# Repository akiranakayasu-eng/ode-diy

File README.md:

# ODE-DIY — 自作の Art-Net / sACN → DMX512 ノード

Art-Net と sACN（E1.31）を LAN で受けて DMX512 を出す、手作りの照明用ノード（「箱」）。照明操作ソフト miseru の画面を本体に内蔵し、ブラウザから WebSocket で照明を動かせる。

A DIY Art-Net / sACN to DMX512 node with a built-in web UI (miseru) over HTTP/WebSocket.

## 版

| 版 | マイコン | 状態 | 場所 |
|---|---|---|---|
| rev A | STM32F407VGT6 + LAN8742A（有線 LAN） | 基板を作って手実装 1 台が動いている。実機に書き込んで動いているのはファーム v0.3.0。このリポジトリのファームは v0.3.6（v0.3.1 以降は試験版（Linux）でだけ確認） | [hardware/revA](hardware/revA/) |
| rev B | ESP32-S3-WROOM-1-N16R8 + W5500（Wi-Fi と有線の併用） | **作業中**。本体の回路図と PCB、天板の回路図と PCB まで（どれも未発注で、まだ直している。版はそれぞれの README）。ファームはこれから | [hardware/revB](hardware/revB/) |

## フォルダ

- `hardware/revA/ode_main/` … rev A の KiCad 一式、ガーバー（JLCPCB 用 4 層）、部品リスト、レビューと立ち上げの記録
- `hardware/revA/case/` … ケース板（天板・底板、基板材で作る）
- `hardware/revB/ode_main/`・`ode_top/` … rev B の本体と天板の回路図・PCB、ケースの寸法モデル、構成案、点検記録
- `firmware/` … ファーム。機種に依らない部分（`app/`）と機種ごとの部分（`port/stm32/`、Linux で試す `port/host/`）に分かれている。rev B は `port/esp32/` を足す予定。ビルド・書き込み・試し方は [firmware/README.md](firmware/README.md)
- `docs/websocket-spec.md` … miseru と箱のあいだの WebSocket とロックの仕様
- `tools/` … 試験用の小さな道具（sACN の送信など）

## できること（rev A、ファーム v0.3.6）

- Art-Net 4（ArtPoll / ArtDmx）と sACN を受けて DMX 1 ユニバースを出す
- 本体に miseru の画面を内蔵（差し替え可）。WebSocket で操作し、送り手を 1 つにロックする
- `/setup` で PIN の変更と画面の差し替え（LOCK ボタン SW2 を 3 秒押してから 10 分の間だけ）。SW2 を 10 秒押すと USB DFU のファーム更新モード（**実機では未確認**）
- 初期値: IP 192.168.1.223、マスク 255.255.255.0、PIN 1234（本体ボタンで初期化）。家の LAN が 192.168.1.x のときは、PC と直結するか番号が重ならないか確かめる

## 基板の図

## ライセンス

- 基板・ケース（`hardware/`）: [CERN-OHL-P-2.0](LICENSE-HARDWARE)。著作者表示は [hardware/NOTICE](hardware/NOTICE)
- 仕様の文書（`docs/websocket-spec.md`）: [MIT](LICENSE-FIRMWARE)。基板の図（`docs/img/`）: [CERN-OHL-P-2.0](LICENSE-HARDWARE)（著作者表示は [hardware/NOTICE](hardware/NOTICE)）
- ファーム・道具・スクリプト（`firmware/`、`tools/`、`hardware/` の中の `*.py`・`*.sh`）: [MIT](LICENSE-FIRMWARE)
- 同梱の外部のもの（それぞれのライセンスに従う）
  - lwIP（BSD-3-Clause、`firmware/vendor/lwip/COPYING`）
  - CMSIS と STM32F4 のデバイスファイル（Apache-2.0、`firmware/vendor/cmsis/LICENSE.txt`・`firmware/vendor/cmsis_f4/LICENSE.md`）。`firmware/port/stm32/startup_stm32f407xx.s` と `system_stm32f4xx.c` も STMicroelectronics 製で Apache-2.0
  - `firmware/app/assets_gen.c` は miseru のビルド済みの画面（ライセンスは公開版 miseru の LICENSE を参照）で、React（MIT）などを含む
  - KiCad 標準ライブラリの記号と足の形（CC-BY-SA 4.0、設計への利用は例外で自由）
- ENTTEC・ODE は ENTTEC 社の商標。このプロジェクトは ENTTEC 社と関係がない

## 注意

個人の手作りの記録です。動作は保証しません。商用の DMX 機器と同じ安全基準での試験はしていません。

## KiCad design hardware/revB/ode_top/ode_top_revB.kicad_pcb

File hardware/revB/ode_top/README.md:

# ode_top rev B（ode_main rev B の天板）回路図 9 版・PCB 2 版（2026-11-23）

天板 = ケースの上の板そのもの（FR-4 1.6mm、2 層）。四隅の M3 スペーサーで本体の上 35mm に留め、側板のつめを長円の穴に差す。ケースの寸法は `../ode_main/case/case_model.py`（v5）。

## 状態

- 回路図 9 版（8 版から部品の Value だけ変えた）: ERC 0、設計意図との照合 0（28 ピン / 11 ネット）。
- PCB 2 版: DRC エラー 0・警告 0・未接続 0（回路図との照合込み）。本体 PCB 4 版との照合 NG 0（`verify_pcb.txt`）。
- 1 版の別スレッドチェック（高 1・中 0・低 3、`天板チェック_回路図7版_PCB1版_別スレッド_2026-11-23.md`）を直し、8 版・PCB 2 版の再チェックは高 0・中 0・低 3。
- 再チェックの低 3 を直した（9 版）: Value を品番だけにした（用途は回路図の文字に）、スイッチを rev A で買った TL3342F160QG/TR に、J1 を B8B-PH-K-S に、ケーブルを部品表に足した。9 版の再チェックは高 0・中 0・低 1（コンタクトを秋月の P0.5L に直した）。天板はこれで一区切り。

### 1 版のチェックで直した所

| 指摘 | 直したこと |
|---|---|
| 高 1 J1 の並びが n 番どうしのケーブルと合わない（7 版は J1.n に J6.(9−n) の信号。組むと天板に +3V3 が来ず、IO6 が 100Ω で GND、EN が約 1.9V） | J1 のネットを J6 と同じ並びに戻した（回路図 8 版）。J1 は裏のまま 180 度回して、J1.n を J6.n の真上に置いた（PCB 2 版）。照合も「J1.n と J6.n のネットが同じ」を見るように変えた |
| 低 1 LED の明るさが 4〜5 倍違う | 黄緑の R1 を 330Ω、R2 を 220Ω にした（下の表） |
| 低 2 品番が回路図に無い | LED・スイッチ・J1 の Value に品番を入れた |
| 低 3 README の LAN の抵抗の部品番号 | R84 に直した |

## J1 とケーブル

ケーブルは JST PH 8P の両端ハウジング、n 番どうし（線 n がハウジングの n 番どうしをつなぐ）。ハウジングの n 番はヘッダーの n 番に入るので、電気的には J1.n = J6.n になる。並びは J6 と同じ。

| J1・J6 | 1 | 2 | 3 | 4 | 5 | 6 | 7 | 8 |
|---|---|---|---|---|---|---|---|---|
| ネット | +3V3 | GND | EN_PANEL | BTN_LOCK | LED_LAN | LED_DMX | LED_LOCK | 予備 |

- J1 は裏で、J1.n が J6.n の真上に来る向き（J6 を並びの軸のまわりに裏返した向き）。本体の広い側（ロックの側）は J6 と逆の前を向く。このため、本体の前後の位置は J6 の真上から 0.7mm ずれる（`verify_pcb.txt` の参考の行）。
- 長さは本体の上面から天板の下まで約 35mm、コネクタの高さを引いて 50mm 前後のケーブルを曲げて入れる。

## 座標

上から見た図で、前（コネクタの面）が画面の下。x はケースの x と同じ（前から見て右へ）なので、表の文字は前から読める。本体 PCB の点 (xm, ym) は天板では (82.6 − xm, 108.6 − ym)。

- 外形 89.2 × 112.7、角 R2。M3 穴 (79.1, 49.1) (10.1, 50.6) (10.1, 28.1) (33.1, 28.1)（本体の穴の真上）。
- 側板のつめの穴 8 つ: 長さ 12.0・幅 1.8 の長円（10.2 × 1.8 の長方形が入る。加工の丸みでつめの角が当たらないように端を半円にした）。中心は `verify_pcb.txt`。

## 部品

前から見て左から DMX｜LAN｜LOCK（LED）｜LOCK｜RESET（ボタン）｜PWR（LED）。PWR は USB-C の上、DMX は XLR の側。

| 部品番号 | シルク | 品 | 購入先 | 電流 |
|---|---|---|---|---|
| D1 | PWR | 黄緑 2012 OSG80805C1C（VF 2.0V） | 秋月 106421 | (3.3−2.0)/330 = 3.9mA |
| D2 | LAN | 黄緑 2012 OSG80805C1C | 秋月 106421 | (3.3−2.0)/(220+100) = 4.1mA（本体 R84 100Ω も通る） |
| D3 | DMX | 黄 2012 OSY50805C1C（VF 2.1V） | 秋月 106420 | (3.3−2.1)/(680+100) = 1.5mA（本体 R85） |
| D4 | LOCK | 赤 2012 OSR50805C1C（VF 2.0V） | 秋月 106419 | (3.3−2.0)/(680+100) = 1.7mA（本体 R86） |
| R1 / R2 / R3・R4 | | 330Ω / 220Ω / 680Ω 0805 | | |
| SW1 | LOCK | TL3342F160QG/TR（rev A で買ったものと同じ） | Digi-Key EG2531CT-ND | |
| SW2 | RESET | TL3342F160QG/TR | Digi-Key EG2531CT-ND | |
| J1 | | JST B8B-PH-K-S（裏） | | |
| ケーブル | | JST PH 8P の両端ケーブル、n 番どうし、50mm 前後。作るなら ハウジング PHR-8 × 2・コンタクト SPH-002T-P0.5L × 16（秋月で扱う品、電線 AWG 28〜24）・電線 × 8 | | |

- J1 の末尾 -S とケーブルの部品の品番は、JST のデータシートが作業環境から読めず確かめていない。
- VF は秋月の商品ページの値（11/23 に在庫ありを確認）。3.3V で点けるので VF 3V 級（純緑・青・白）は使わない。明るさ（20mA の typ × 電流の比）: 黄緑 約 4〜7mcd、黄 約 8mcd、赤 約 13mcd。1 版（黄緑 約 3mcd）より近づけた。組んでそろわなければ R を変える。
- 回路図 1 版で書いた「RESET はクリップで押す」はやめた。表に付けたボタンは指で押せる。天板の表だけでは、穴の奥に沈めたボタンを作れないため。本体にも RESET（本体 SW1）がある。

## 配線

裏: J1 から前へ下ろし、部品の手前でビアで表へ（LED_DMX・LED_LAN・+3V3・EN_PANEL・BTN_LOCK）。LED_LOCK は裏の線をまたぐので表だけで引いた。表と裏は GND ベタ（最小幅 0.5、サーマルのスポーク 0.5）、GND のつなぎビア 78 本（10mm おき）。線 0.3mm、ビア φ0.6 / 0.3。

## 作り直し

```
KICAD_SYMDIR=<KiCad 10 の symbols> python3 scripts/gen_sch.py（2 回）→ sh run_erc.sh
docker の kicad/kicad:10.0 の中で sh scripts/all.sh（基板 → DRC → 本体との照合 → 確認図。../ode_main_revB が要る）
```

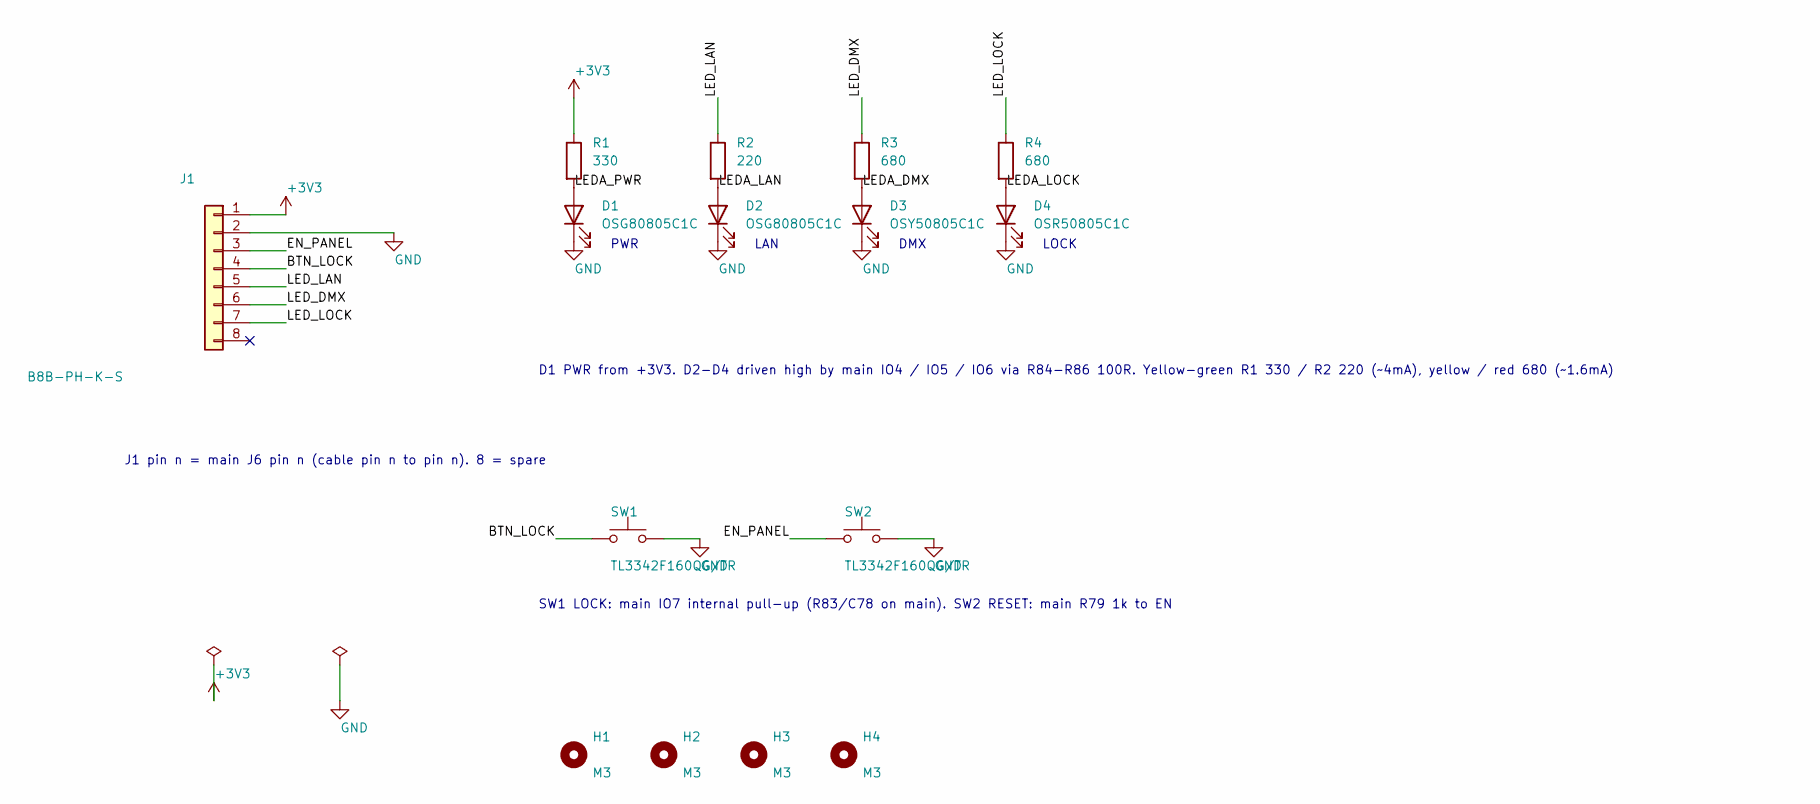
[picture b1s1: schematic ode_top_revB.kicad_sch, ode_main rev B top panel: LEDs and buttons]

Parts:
D1, D2: OSG80805C1C; LED_0805_2012Metric_Pad1.15x1.40mm_HandSolder
D3: OSY50805C1C; LED_0805_2012Metric_Pad1.15x1.40mm_HandSolder
D4: OSR50805C1C; LED_0805_2012Metric_Pad1.15x1.40mm_HandSolder
H1, H2, H3, H4: M3; MountingHole_3.2mm_M3
J1: B8B-PH-K-S; JST_PH_B8B-PH-K_1x08_P2.00mm_Vertical
R1: 330; R_0805_2012Metric_Pad1.20x1.40mm_HandSolder
R2: 220; R_0805_2012Metric_Pad1.20x1.40mm_HandSolder
R3, R4: 680; R_0805_2012Metric_Pad1.20x1.40mm_HandSolder
SW1, SW2: TL3342F160QG/TR; SW_SPST_TL3342

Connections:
+3V3: J1.1, R1.1
/BTN_LOCK: J1.4, SW1.1
/EN_PANEL: J1.3, SW2.1
/LEDA_DMX: D3.2 (A), R3.2
/LEDA_LAN: D2.2 (A), R2.2
/LEDA_LOCK: D4.2 (A), R4.2
/LEDA_PWR: D1.2 (A), R1.2
/LED_DMX: J1.6, R3.1
/LED_LAN: J1.5, R2.1
/LED_LOCK: J1.7, R4.1
GND: D1.1 (K), D2.1 (K), D3.1 (K), D4.1 (K), J1.2, SW1.2, SW2.2

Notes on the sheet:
J1 pin n = main J6 pin n (cable pin n to pin n). 8 = spare
PWR
LAN
DMX
LOCK
D1 PWR from +3V3. D2-D4 driven high by main IO4 / IO5 / IO6 via R84-R86 100R. Yellow-green R1 330 / R2 220 (~4mA), yellow / red 680 (~1.6mA)
SW1 LOCK: main IO7 internal pull-up (R83/C78 on main). SW2 RESET: main R79 1k to EN

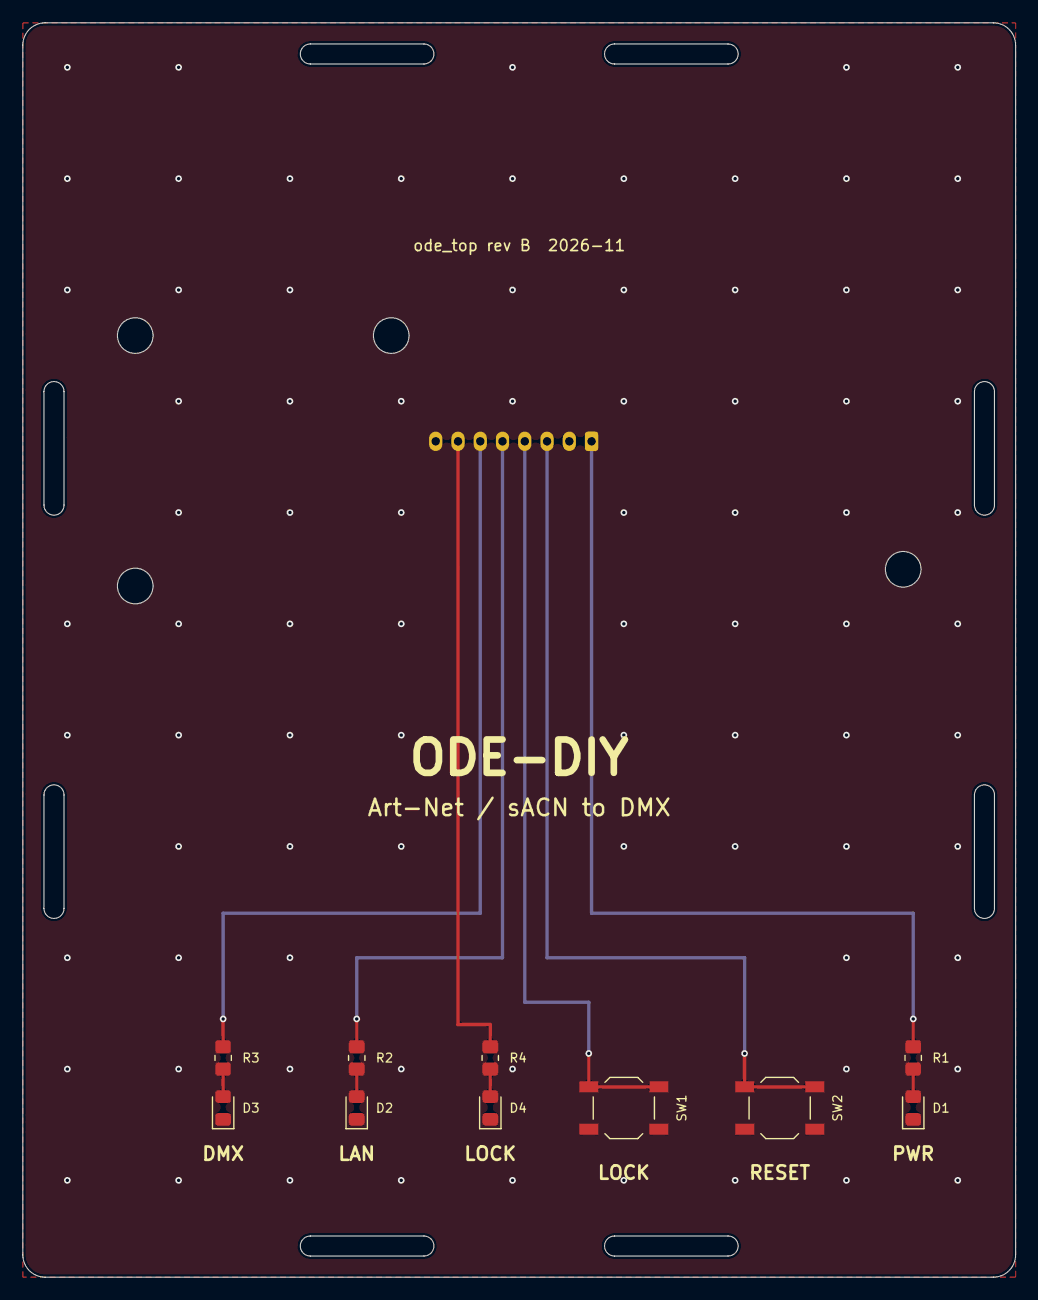
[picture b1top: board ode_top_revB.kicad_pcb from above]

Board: 2 copper layers, 89.2 x 112.7 mm, 15 parts (1 on the bottom side), 11 nets.
